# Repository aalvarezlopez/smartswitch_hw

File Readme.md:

# Issues found while testing the first version

* Resisor package is 0201, change it to 0603
* I2C pins are located in a invalid pin. Correct location is:
   * TWD0 SPI\_SDA => PA3 
   * TWCK SPI\_CLK PA4
* I2C pull up resistors are missed (4k7)
* SPI pins are located in a invalid pin. Correct location is:
    * MISO => PA12
    * MOSI => PA13
    * SPCK => PA14
* DS18B20 can be serialized. Hot/Cold temperature of each radiator could use the same bus

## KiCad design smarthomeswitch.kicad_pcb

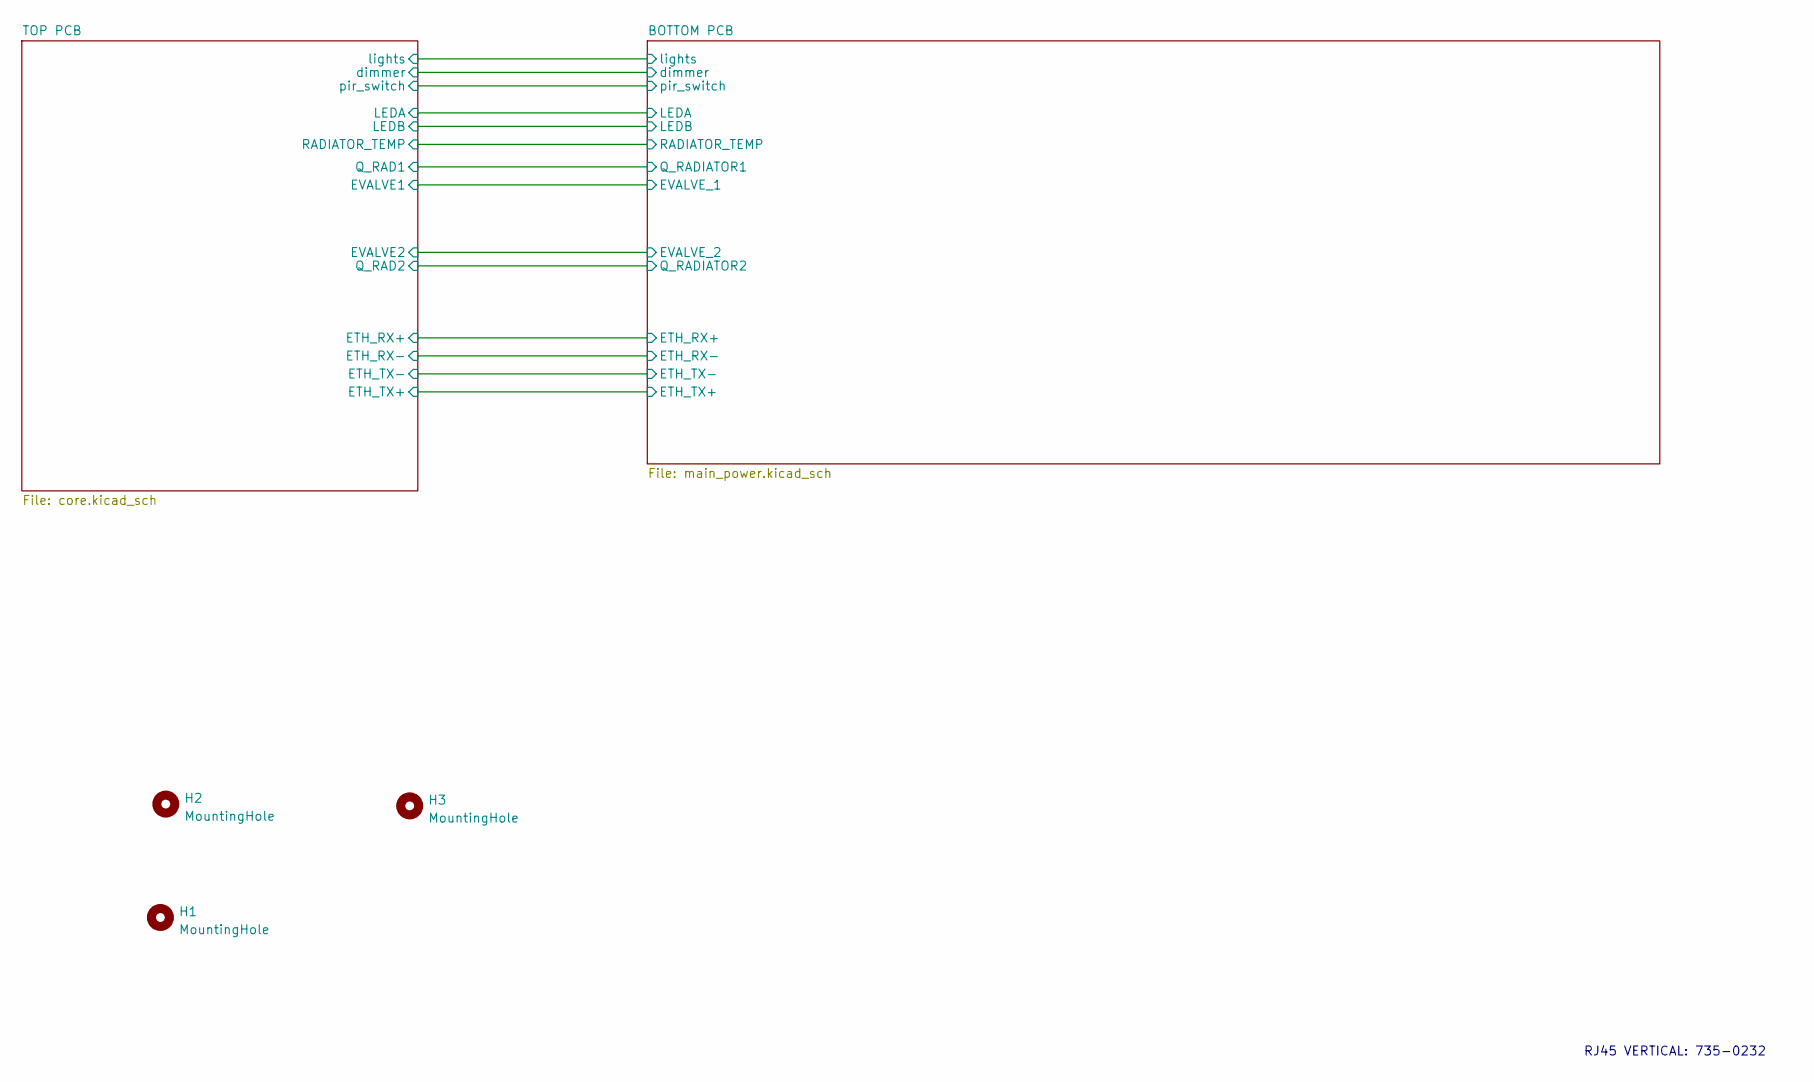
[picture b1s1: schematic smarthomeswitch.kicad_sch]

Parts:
H1, H2, H3: MountingHole; MountingHole_3.2mm_M3_ISO14580

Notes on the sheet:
RJ45 VERTICAL: 735-0232

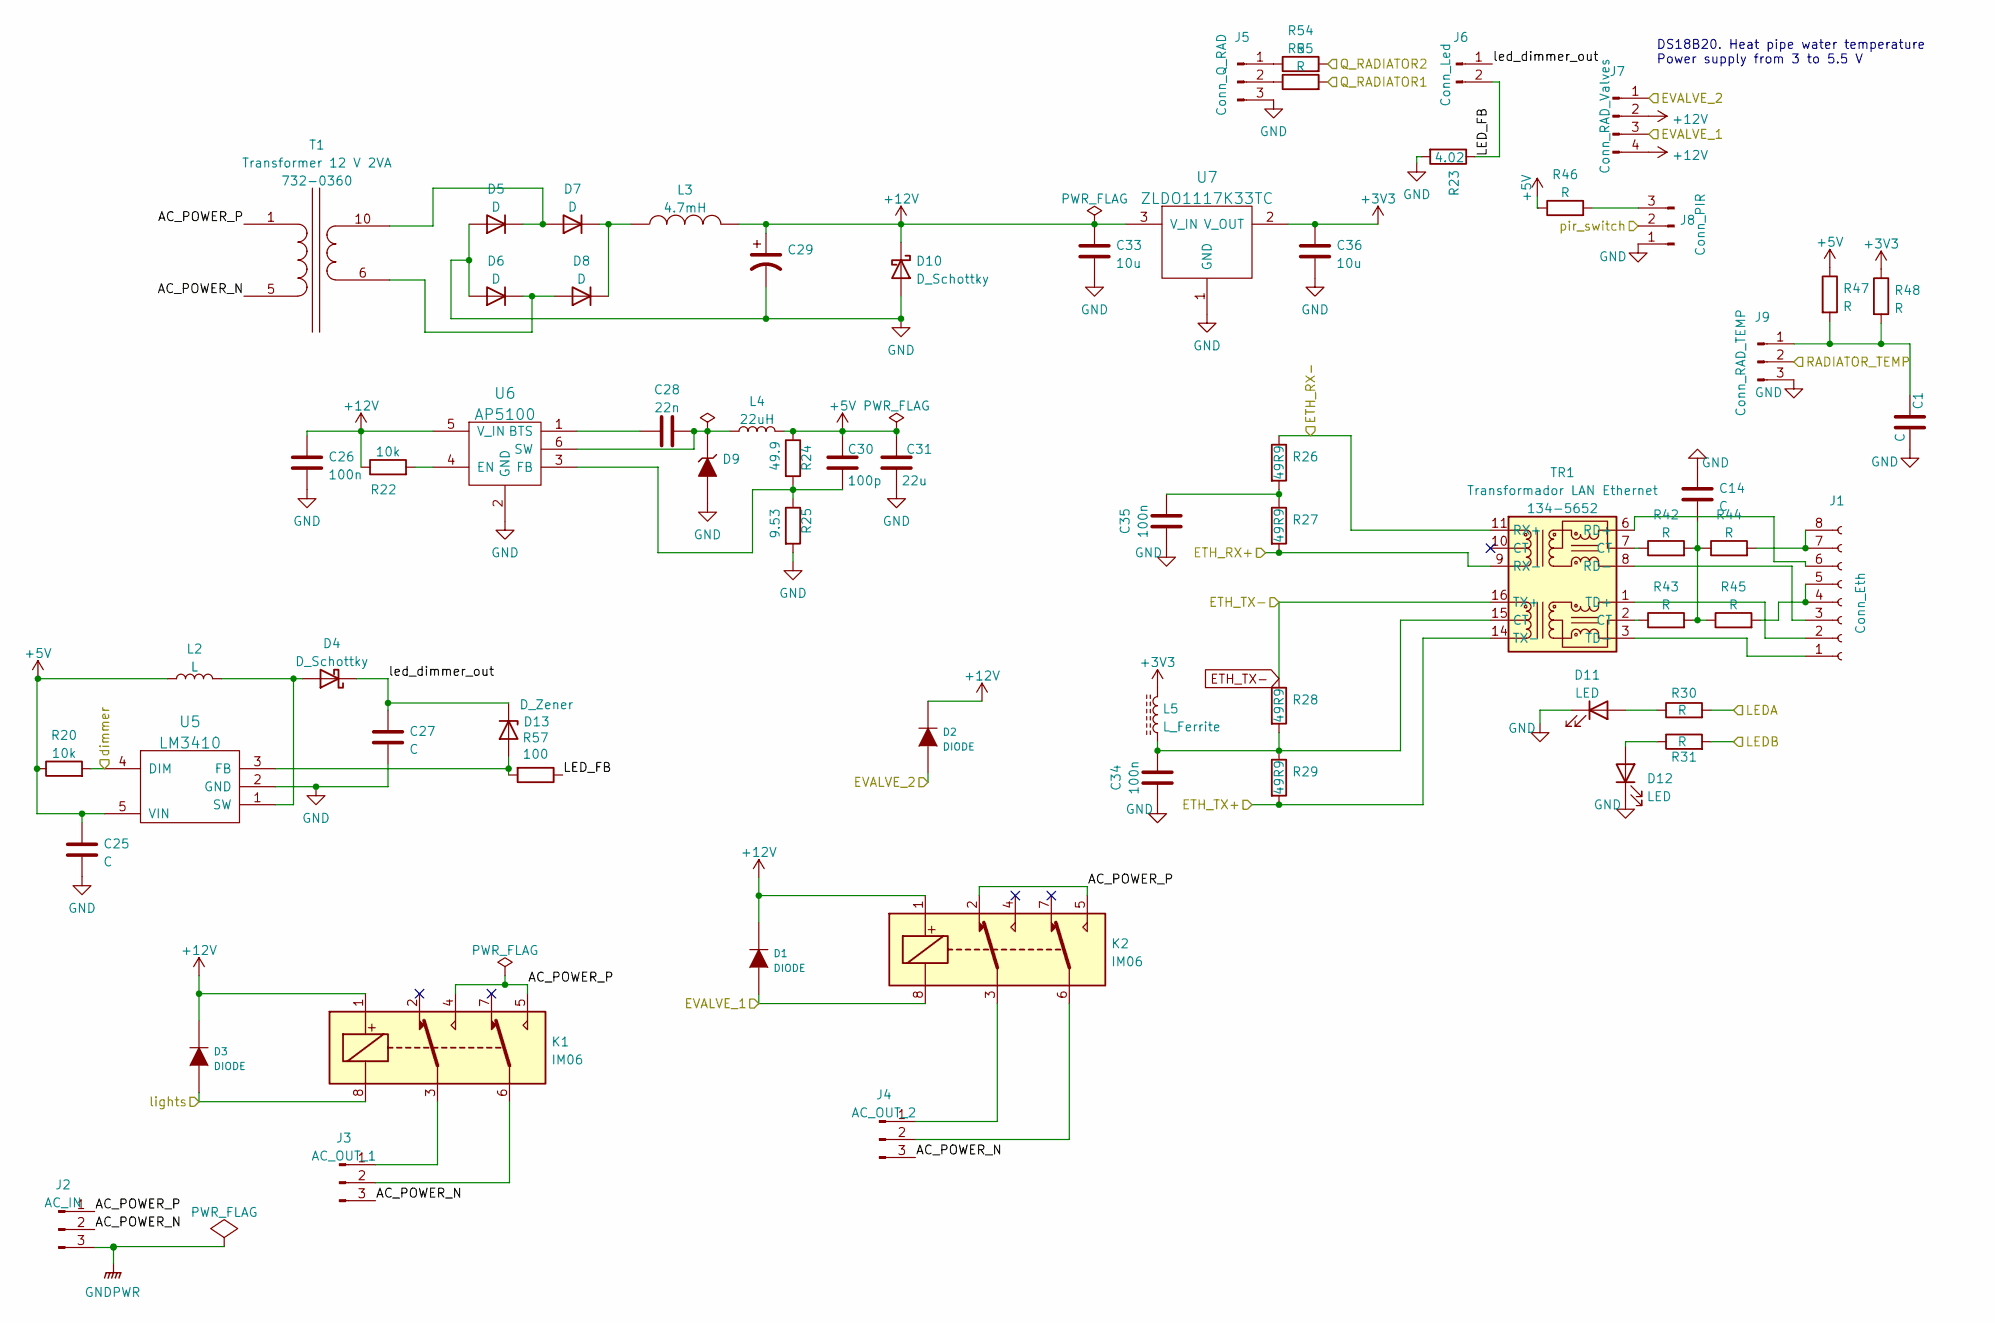
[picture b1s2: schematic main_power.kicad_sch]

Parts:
C1, C14, C25, C27: C; C_0603_1608Metric_Pad1.08x0.95mm_HandSolder
C26, C34, C35: 100n; C_0603_1608Metric_Pad1.08x0.95mm_HandSolder
C28: 22n; C_0603_1608Metric_Pad1.08x0.95mm_HandSolder
C29: C_Polarized_US; CP_Elec_6.3x5.8
C30: 100p; C_0603_1608Metric_Pad1.08x0.95mm_HandSolder
C31: 22u; CP_EIA-6032-15_Kemet-U_Pad2.25x2.35mm_HandSolder
C33, C36: 10u; CP_EIA-3528-12_Kemet-T_Pad1.50x2.35mm_HandSolder
D1, D2, D3: DIODE; D_SMA
D4: D_Schottky; D_Powermite2_AK
D5, D6, D7, D8: D; DO-213AB
D9: ZENER; D_SOD-323
D10: D_Schottky; D_SMA
D11, D12: LED; LED_0603_1608Metric_Pad1.05x0.95mm_HandSolder
D13: D_Zener; D_SMA_Handsoldering
J1: Conn_Eth; PinHeader_1x08_P2.54mm_Vertical
J2: AC_IN; TerminalBlock_bornier-3_P5.08mm
J3: AC_OUT_1; TerminalBlock_bornier-3_P5.08mm
J4: AC_OUT_2; TerminalBlock_bornier-3_P5.08mm
J5: Conn_Q_RAD; JST_PH_B3B-PH-K_1x03_P2.00mm_Vertical
J6: Conn_Led; JST_PH_B2B-PH-K_1x02_P2.00mm_Vertical
J7: Conn_RAD_Valves; JST_PH_B4B-PH-K_1x04_P2.00mm_Vertical
J8: Conn_PIR; JST_PH_B3B-PH-K_1x03_P2.00mm_Vertical
J9: Conn_RAD_TEMP; JST_PH_B3B-PH-K_1x03_P2.00mm_Vertical
K1, K2: IM06; IM06CTS
L2: L; L_1210_3225Metric_Pad1.42x2.65mm_HandSolder
L3: 4.7mH; L_12x12mm_H8mm
L4: 22uH; L_Wuerth_WE-PD2-Typ-L
L5: L_Ferrite; L_0805_2012Metric_Pad1.15x1.40mm_HandSolder
R20, R22: 10k; R_0603_1608Metric_Pad0.98x0.95mm_HandSolder
R23: 4.02; R_0603_1608Metric_Pad0.98x0.95mm_HandSolder
R24: 49.9; R_0603_1608Metric_Pad0.98x0.95mm_HandSolder
R25: 9.53; R_0603_1608Metric_Pad0.98x0.95mm_HandSolder
R26, R27, R28, R29: 49R9; R_0603_1608Metric_Pad0.98x0.95mm_HandSolder
R30, R31, R42, R43, R44, R45, R46, R47, R48, R54, R55: R; R_0603_1608Metric_Pad0.98x0.95mm_HandSolder
R57: 100; R_0603_1608Metric_Pad0.98x0.95mm_HandSolder
T1: Transformer 12 V 2VA; 12v_transformer_single
TR1: Transformador LAN Ethernet; SM13072APEL
U5: LM3410; SOT-23-5_HandSoldering
U6: AP5100; SOT26
U7: ZLDO1117K33TC; TO-252-3_TabPin2

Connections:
+3V3: C36.1, L5.2, R48.1, U7.2 (V_OUT); also elsewhere on the board
+5V: C25.1, C30.1, C31.1, L2.1, L4.2, R20.1, R24.1, R46.1, R47.1, U5.5 (VIN)
+12V: C26.1, C29.1, C33.1, D1.2 (K), D2.2 (K), D3.2 (K), D10.1 (K), J7.2, J7.4, K1.1, K2.1, L3.2, R22.1, U6.5 (V_IN), U7.3 (V_IN)
/BOTTOM PCB/AC_POWER_N: J2.2, J3.3, J4.3, T1.5 (AB)
/BOTTOM PCB/AC_POWER_P: J2.1, K1.4, K1.5, K2.2, K2.5, T1.1 (AA)
/BOTTOM PCB/EVALVE_1: D1.1 (A), J7.3, K2.8; also elsewhere on the board
/BOTTOM PCB/EVALVE_2: D2.1 (A), J7.1; also elsewhere on the board
/BOTTOM PCB/LEDA: R30.2; also elsewhere on the board
/BOTTOM PCB/LEDB: R31.2; also elsewhere on the board
/BOTTOM PCB/LED_FB: J6.2, R23.1, R57.1
/BOTTOM PCB/Q_RADIATOR1: R55.2; also elsewhere on the board
/BOTTOM PCB/Q_RADIATOR2: R54.2; also elsewhere on the board
/BOTTOM PCB/RADIATOR_TEMP: J9.2; also elsewhere on the board
/BOTTOM PCB/dimmer: R20.2, U5.4 (DIM); also elsewhere on the board
/BOTTOM PCB/led_dimmer_out: C27.1, D4.1 (K), D13.1 (K), J6.1
/BOTTOM PCB/lights: D3.1 (A), K1.8; also elsewhere on the board
/BOTTOM PCB/pir_switch: J8.2; also elsewhere on the board
/TOP PCB/ethernet/ETH_RX+: R27.2, TR1.9 (RX-); also elsewhere on the board
/TOP PCB/ethernet/ETH_RX-: R26.1, TR1.11 (RX+); also elsewhere on the board
/TOP PCB/ethernet/ETH_TX+: R29.2, TR1.14 (TX-); also elsewhere on the board
ETH_TX-: R28.1, TR1.16 (TX+); also elsewhere on the board
GND: C1.2, C14.1, C25.2, C26.2, C27.2, C29.2, C31.2, C33.2, C34.1, C35.1, C36.2, D5.2 (A), D6.2 (A), D9.2 (A), D10.2 (A), D11.1 (K), D12.1 (K), J5.3, J8.1, J9.3, R23.2, R25.2, U5.2 (GND), U6.2 (GND), U7.1 (GND); also elsewhere on the board
GNDPWR: J2.3
unnamed: C1.1, J9.1, R47.2, R48.2
unnamed: C14.2, R42.2, R43.2, R44.1, R45.1
unnamed: C28.1, U6.1 (BTS)
unnamed: C28.2, D9.1 (K), L4.1, U6.6 (SW)
unnamed: C30.2, R24.2, R25.1, U6.3 (FB)
unnamed: C34.2, L5.1, R28.2, R29.1, TR1.15 (CT)
unnamed: C35.2, R26.2, R27.1
unnamed: D4.2 (A), L2.2, U5.1 (SW)
unnamed: D5.1 (K), D7.2 (A), T1.10 (SA)
unnamed: D6.1 (K), D8.2 (A), T1.6 (SD)
unnamed: D7.1 (K), D8.1 (K), L3.1
unnamed: D11.2 (A), R30.1
unnamed: D12.2 (A), R31.1
unnamed: D13.2 (A), R57.2, U5.3 (FB)
unnamed: J1.1, TR1.3 (TD-)
unnamed: J1.2, TR1.1 (TD+)
unnamed: J1.3, TR1.8 (RD-)
unnamed: J1.4, J1.5, R45.2
unnamed: J1.6, TR1.6 (RD+)
unnamed: J1.7, J1.8, R44.2
unnamed: J3.1, K1.3
unnamed: J3.2, K1.6
unnamed: J4.1, K2.3
unnamed: J4.2, K2.6
unnamed: J5.1, R54.1
unnamed: J5.2, R55.1
unnamed: J8.3, R46.2
unnamed: R22.2, U6.4 (EN)
unnamed: R42.1, TR1.7 (CT)
unnamed: R43.1, TR1.2 (CT)

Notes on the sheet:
DS18B20. Heat pipe water temperature Power supply from 3 to 5.5 V

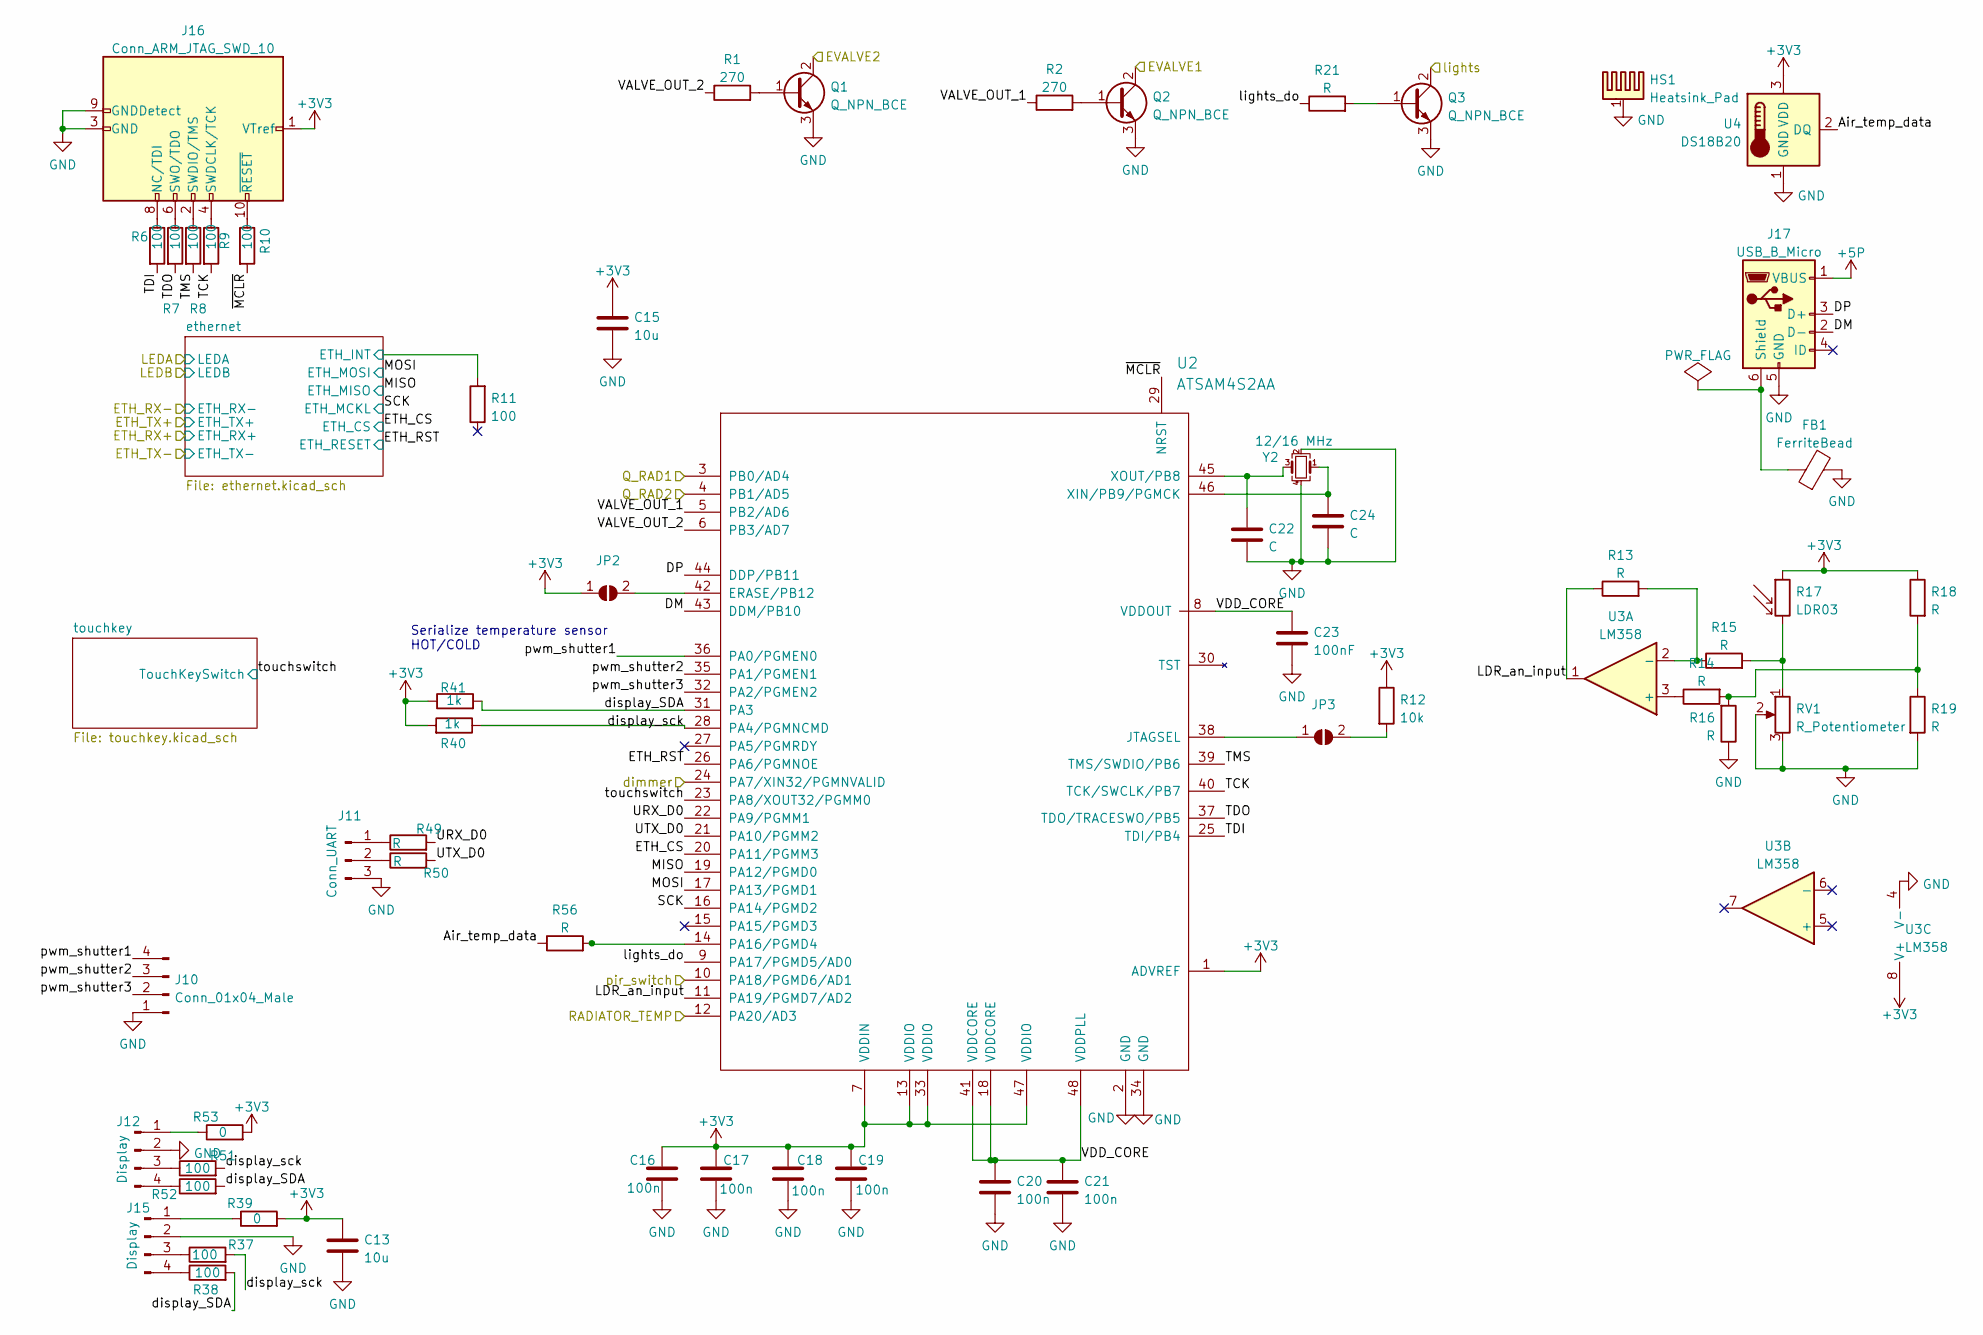
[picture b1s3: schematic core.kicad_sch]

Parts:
C13, C15: 10u; CP_EIA-3528-12_Kemet-T_Pad1.50x2.35mm_HandSolder
C16, C17, C18, C19, C20, C21: 100n; C_0603_1608Metric_Pad1.08x0.95mm_HandSolder
C22, C24: C; C_0603_1608Metric_Pad1.08x0.95mm_HandSolder
C23: 100nF; C_0603_1608Metric_Pad1.08x0.95mm_HandSolder
FB1: FerriteBead; L_1206_3216Metric_Pad1.22x1.90mm_HandSolder
HS1: Heatsink_Pad; Heatsink_AAVID_573300D00010G_TO-263
J10: Conn_01x04_Male; JST_PH_B4B-PH-K_1x04_P2.00mm_Vertical
J11: Conn_UART; JST_PH_B3B-PH-K_1x03_P2.00mm_Vertical
J12, J15: Display; PinHeader_1x04_P2.54mm_Vertical
J16: Conn_ARM_JTAG_SWD_10; JTAG_50mil
J17: USB_B_Micro; USB_Micro-B_Molex_47346-0001
JP2, JP3: SolderJumper_2_Open; SolderJumper-2_P1.3mm_Open_TrianglePad1.0x1.5mm
Q1, Q2, Q3: Q_NPN_BCE; SOT-223-3_TabPin2
R1, R2: 270; R_0603_1608Metric_Pad0.98x0.95mm_HandSolder
R6, R7, R8, R9, R10, R11, R37, R38, R51, R52: 100; R_0603_1608Metric_Pad0.98x0.95mm_HandSolder
R12: 10k; R_0603_1608Metric_Pad0.98x0.95mm_HandSolder
R13, R14, R15, R16, R18, R19, R21, R49, R50, R56: R; R_0603_1608Metric_Pad0.98x0.95mm_HandSolder
R17: LDR03; R_Axial_DIN0204_L3.6mm_D1.6mm_P1.90mm_Vertical
R39, R53: 0; R_0603_1608Metric_Pad0.98x0.95mm_HandSolder
R40, R41: 1k; R_0603_1608Metric_Pad0.98x0.95mm_HandSolder
RV1: R_Potentiometer; Potentiometer_Bourns_TC33X_Vertical
U2: ATSAM4S2AA; LQFP-48_7x7mm_P0.5mm
U3: LM358; SOIC-8_3.9x4.9mm_P1.27mm
U4: DS18B20; TO-92_Inline
Y2: 12/16 MHz; Crystal_SMD_5032-4Pin_5.0x3.2mm

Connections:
+3V3: C13.1, C15.1, C16.1, C17.1, C18.1, C19.1, J16.1 (VTref), JP2.1 (A), R12.1, R17.1, R18.1, R39.2, R40.2, R41.1, R53.2, U2.1 (ADVREF), U2.7 (VDDIN), U2.13 (VDDIO), U2.33 (VDDIO), U2.47 (VDDIO), U3.8 (V+), U4.3 (VDD); also elsewhere on the board
+5P: J17.1 (VBUS)
/BOTTOM PCB/EVALVE_1: Q2.2 (C); also elsewhere on the board
/BOTTOM PCB/EVALVE_2: Q1.2 (C); also elsewhere on the board
/BOTTOM PCB/Q_RADIATOR1: U2.3 (PB0/AD4); also elsewhere on the board
/BOTTOM PCB/Q_RADIATOR2: U2.4 (PB1/AD5); also elsewhere on the board
/BOTTOM PCB/RADIATOR_TEMP: U2.12 (PA20/AD3); also elsewhere on the board
/BOTTOM PCB/dimmer: U2.24 (PA7/XIN32/PGMNVALID); also elsewhere on the board
/BOTTOM PCB/lights: Q3.2 (C); also elsewhere on the board
/BOTTOM PCB/pir_switch: U2.10 (PA18/PGMD6/AD1); also elsewhere on the board
/TOP PCB/Air_temp_data: R56.1, U4.2 (DQ)
/TOP PCB/DM: J17.2 (D-), U2.43 (DDM/PB10)
/TOP PCB/DP: J17.3 (D+), U2.44 (DDP/PB11)
/TOP PCB/ETH_CS: U2.20 (PA11/PGMM3); also elsewhere on the board
/TOP PCB/ETH_RST: U2.26 (PA6/PGMNOE); also elsewhere on the board
/TOP PCB/LDR_an_input: R13.1, U2.11 (PA19/PGMD7/AD2), U3.1
/TOP PCB/MISO: U2.19 (PA12/PGMD0); also elsewhere on the board
/TOP PCB/MOSI: U2.17 (PA13/PGMD1); also elsewhere on the board
/TOP PCB/SCK: U2.16 (PA14/PGMD2); also elsewhere on the board
/TOP PCB/TCK: R9.2, U2.40 (TCK/SWCLK/PB7)
/TOP PCB/TDI: R6.2, U2.25 (TDI/PB4)
/TOP PCB/TDO: R7.2, U2.37 (TDO/TRACESWO/PB5)
/TOP PCB/TMS: R8.2, U2.39 (TMS/SWDIO/PB6)
/TOP PCB/URX_D0: R49.2, U2.22 (PA9/PGMM1)
/TOP PCB/UTX_D0: R50.2, U2.21 (PA10/PGMM2)
/TOP PCB/VALVE_OUT_1: R2.1, U2.5 (PB2/AD6)
/TOP PCB/VALVE_OUT_2: R1.1, U2.6 (PB3/AD7)
/TOP PCB/VDD_CORE: C20.1, C21.1, C23.1, U2.8 (VDDOUT), U2.18 (VDDCORE), U2.41 (VDDCORE), U2.48 (VDDPLL)
/TOP PCB/display_SDA: R38.2, R41.2, R52.2, U2.31 (PA3)
/TOP PCB/display_sck: R37.2, R40.1, R51.2, U2.28 (PA4/PGMNCMD)
/TOP PCB/ethernet/ETH_INT: R11.2; also elsewhere on the board
/TOP PCB/lights_do: R21.1, U2.9 (PA17/PGMD5/AD0)
/TOP PCB/pwm_shutter1: J10.4, U2.36 (PA0/PGMEN0)
/TOP PCB/pwm_shutter2: J10.3, U2.35 (PA1/PGMEN1)
/TOP PCB/pwm_shutter3: J10.2, U2.32 (PA2/PGMEN2)
/TOP PCB/touchswitch: U2.23 (PA8/XOUT32/PGMM0); also elsewhere on the board
/TOP PCB/~MCLR: R10.2, U2.29 (NRST)
GND: C13.2, C15.2, C16.2, C17.2, C18.2, C19.2, C20.2, C21.2, C22.2, C23.2, C24.2, FB1.2, HS1.1, J10.1, J11.3, J12.2, J15.2, J16.3 (GND), J16.5 (GND), J16.9 (GNDDetect), J17.5 (GND), Q1.3 (E), Q2.3 (E), Q3.3 (E), R16.1, R19.2, RV1.2, RV1.3, U2.2 (GND), U2.34 (GND), U3.4 (V-), U4.1 (GND), Y2.2, Y2.4; also elsewhere on the board
unnamed: C22.1, U2.45 (XOUT/PB8), Y2.3
unnamed: C24.1, U2.46 (XIN/PB9/PGMCK), Y2.1
unnamed: FB1.1, J17.6 (Shield)
unnamed: J11.1, R49.1
unnamed: J11.2, R50.1
unnamed: J12.1, R53.1
unnamed: J12.3, R51.1
unnamed: J12.4, R52.1
unnamed: J15.1, R39.1
unnamed: J15.3, R37.1
unnamed: J15.4, R38.1
unnamed: J16.2 (SWDIO/TMS), R8.1
unnamed: J16.4 (SWDCLK/TCK), R9.1
unnamed: J16.6 (SWO/TDO), R7.1
unnamed: J16.8 (NC/TDI), R6.1
unnamed: J16.10 (~RESET), R10.1
unnamed: JP2.2 (B), U2.42 (ERASE/PB12)
unnamed: JP3.1 (A), U2.38 (JTAGSEL)
unnamed: JP3.2 (B), R12.2
unnamed: Q1.1 (B), R1.2
unnamed: Q2.1 (B), R2.2
unnamed: Q3.1 (B), R21.2
unnamed: R13.2, R15.1, U3.2 (-)
unnamed: R14.1, U3.3 (+)
unnamed: R14.2, R16.2, R18.2, R19.1
unnamed: R15.2, R17.2, RV1.1
unnamed: R56.2, U2.14 (PA16/PGMD4)

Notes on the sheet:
Serialize temperature sensor HOT/COLD

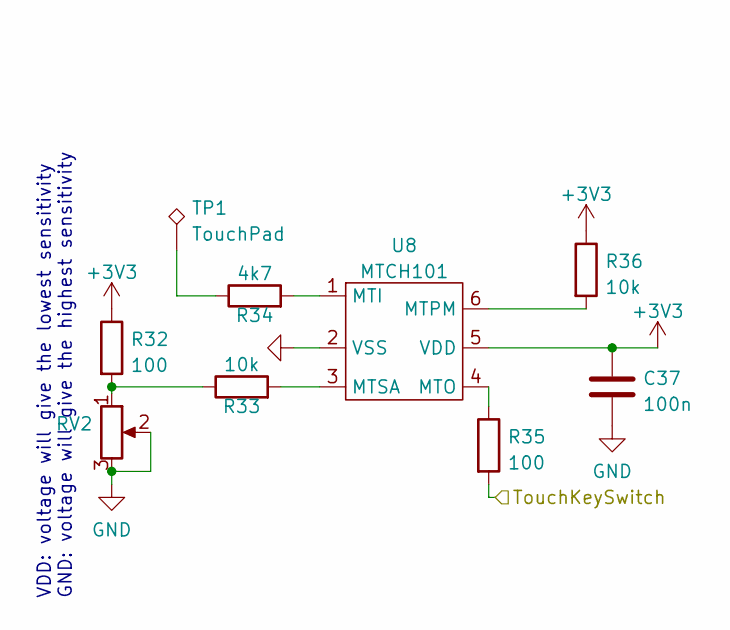
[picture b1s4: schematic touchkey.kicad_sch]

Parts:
C37: 100n; C_0603_1608Metric_Pad1.08x0.95mm_HandSolder
R32, R35: 100; R_0603_1608Metric_Pad0.98x0.95mm_HandSolder
R33, R36: 10k; R_0603_1608Metric_Pad0.98x0.95mm_HandSolder
R34: 4k7; R_0603_1608Metric_Pad0.98x0.95mm_HandSolder
RV2: R_Potentiometer; Potentiometer_Bourns_TC33X_Vertical
TP1: TouchPad; SolderWire-0.15sqmm_1x01_D0.5mm_OD1.5mm
U8: MTCH101; SOT-23-6_Handsoldering

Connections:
+3V3: C37.1, R32.1, R36.1, U8.5 (VDD); also elsewhere on the board
/TOP PCB/touchswitch: R35.2; also elsewhere on the board
GND: C37.2, RV2.2, RV2.3, U8.2 (VSS); also elsewhere on the board
unnamed: R32.2, R33.1, RV2.1
unnamed: R33.2, U8.3 (MTSA)
unnamed: R34.1, TP1.1
unnamed: R34.2, U8.1 (MTI)
unnamed: R35.1, U8.4 (MTO)
unnamed: R36.2, U8.6 (MTPM)

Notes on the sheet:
VDD: voltage will give the lowest sensitivity GND: voltage will give the highest sensitivity

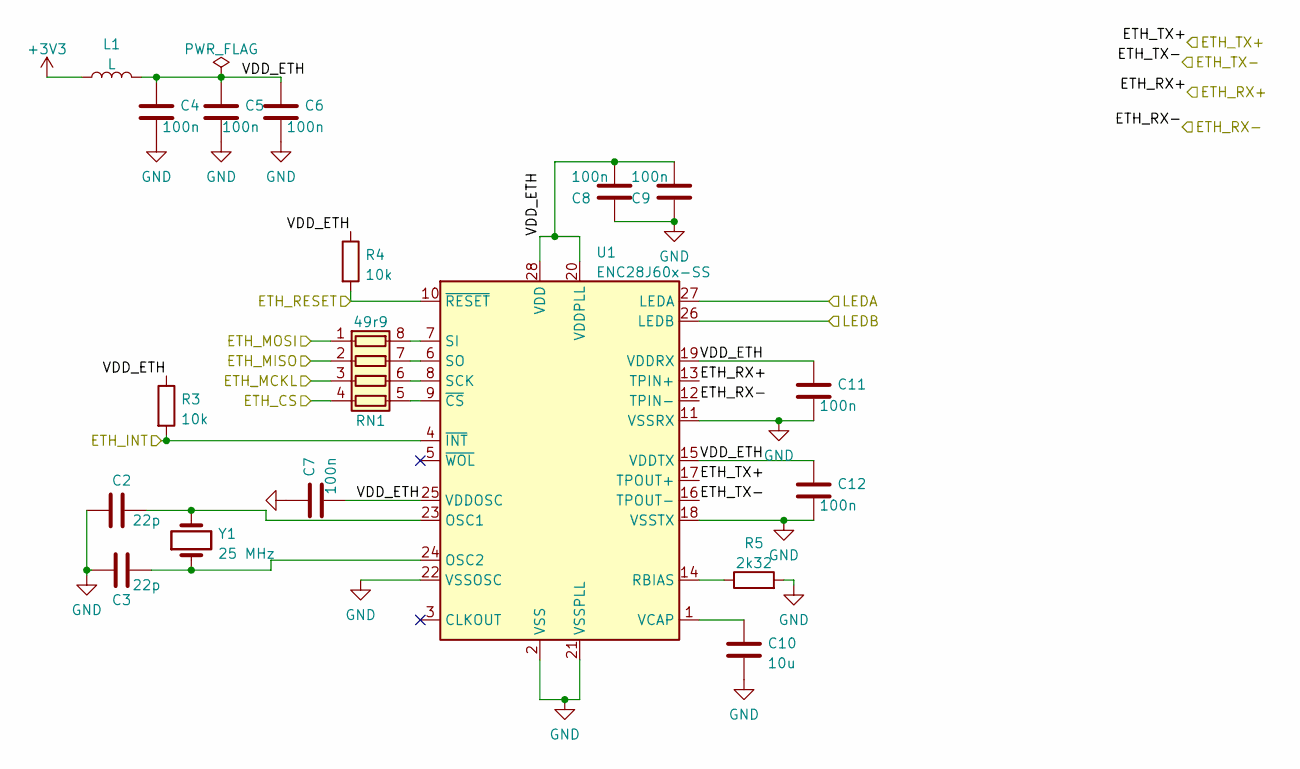
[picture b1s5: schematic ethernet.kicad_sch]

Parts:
C2, C3: 22p; C_0603_1608Metric_Pad1.08x0.95mm_HandSolder
C4, C5, C6, C7, C8, C9, C11, C12: 100n; C_0603_1608Metric_Pad1.08x0.95mm_HandSolder
C10: 10u; CP_EIA-3528-21_Kemet-B_Pad1.50x2.35mm_HandSolder
L1: L; L_0603_1608Metric_Pad1.05x0.95mm_HandSolder
R3, R4: 10k; R_0603_1608Metric_Pad0.98x0.95mm_HandSolder
R5: 2k32; R_0603_1608Metric_Pad0.98x0.95mm_HandSolder
RN1: 49r9; R_Array_Convex_4x0612
U1: ENC28J60x-SS; SSOP-28_5.3x10.2mm_P0.65mm
Y1: 25 MHz; Crystal_SMD_HC49-SD

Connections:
+3V3: L1.1; also elsewhere on the board
/BOTTOM PCB/LEDA: U1.27 (LEDA); also elsewhere on the board
/BOTTOM PCB/LEDB: U1.26 (LEDB); also elsewhere on the board
/TOP PCB/ETH_CS: RN1.4 (R4.1); also elsewhere on the board
/TOP PCB/ETH_RST: R4.2, U1.10 (~RESET); also elsewhere on the board
/TOP PCB/MISO: RN1.2 (R2.1); also elsewhere on the board
/TOP PCB/MOSI: RN1.1 (R1.1); also elsewhere on the board
/TOP PCB/SCK: RN1.3 (R3.1); also elsewhere on the board
/TOP PCB/ethernet/ETH_INT: R3.2, U1.4 (~INT); also elsewhere on the board
/TOP PCB/ethernet/ETH_RX+: U1.13 (TPIN+); also elsewhere on the board
/TOP PCB/ethernet/ETH_RX-: U1.12 (TPIN-); also elsewhere on the board
/TOP PCB/ethernet/ETH_TX+: U1.17 (TPOUT+); also elsewhere on the board
/TOP PCB/ethernet/VDD_ETH: C4.1, C5.1, C6.1, C7.2, C8.2, C9.2, C11.1, C12.1, L1.2, R3.1, R4.1, U1.15 (VDDTX), U1.19 (VDDRX), U1.20 (VDDPLL), U1.25 (VDDOSC), U1.28 (VDD)
ETH_TX-: U1.16 (TPOUT-); also elsewhere on the board
GND: C2.1, C3.1, C4.2, C5.2, C6.2, C7.1, C8.1, C9.1, C10.2, C11.2, C12.2, R5.2, U1.2 (VSS), U1.11 (VSSRX), U1.18 (VSSTX), U1.21 (VSSPLL), U1.22 (VSSOSC); also elsewhere on the board
unnamed: C2.2, U1.23 (OSC1), Y1.2
unnamed: C3.2, U1.24 (OSC2), Y1.1
unnamed: C10.1, U1.1 (VCAP)
unnamed: R5.1, U1.14 (RBIAS)
unnamed: RN1.5 (R4.2), U1.9 (~CS)
unnamed: RN1.6 (R3.2), U1.8 (SCK)
unnamed: RN1.7 (R2.2), U1.6 (SO)
unnamed: RN1.8 (R1.2), U1.7 (SI)

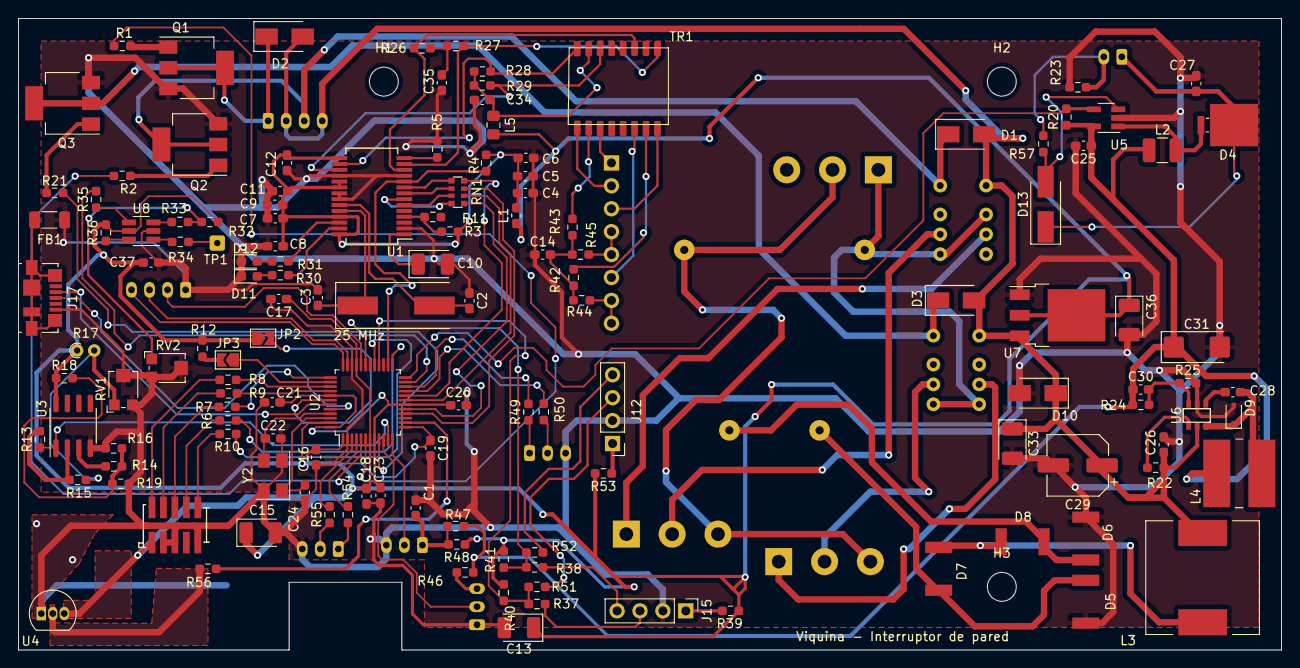
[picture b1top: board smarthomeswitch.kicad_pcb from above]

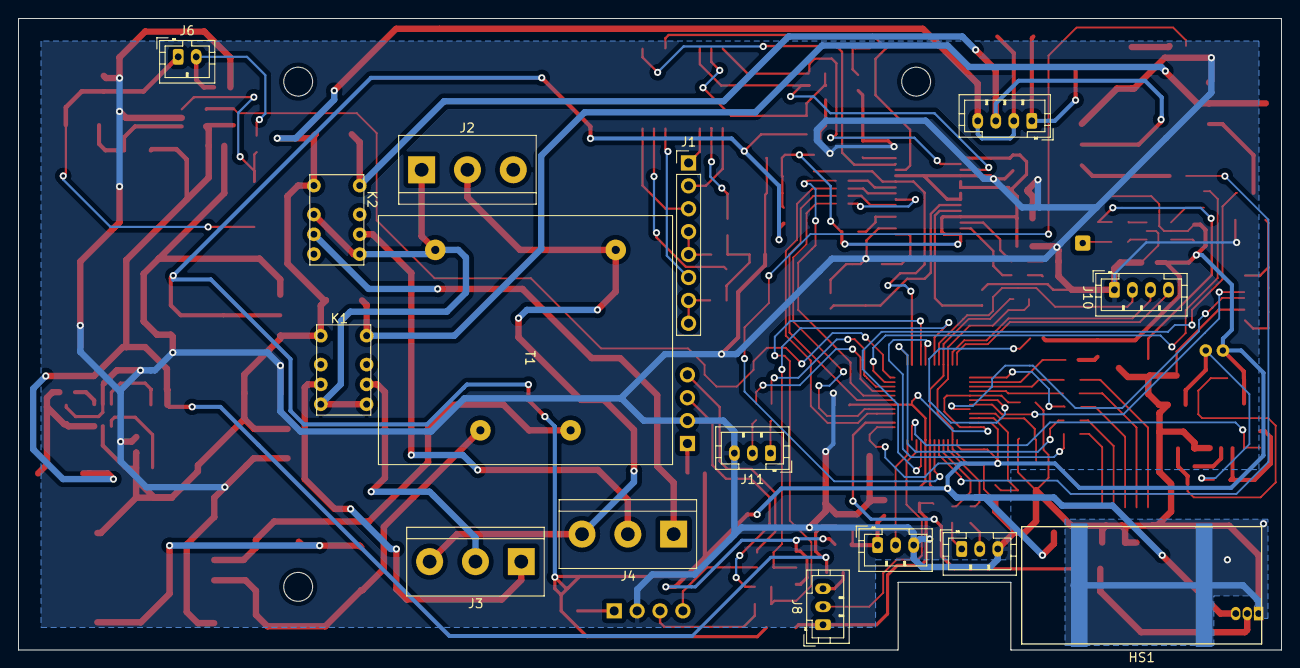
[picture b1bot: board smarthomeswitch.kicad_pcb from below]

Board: 2 copper layers, 140.0 x 70.0 mm, 154 parts (15 on the bottom side), 121 nets.

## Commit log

2023-11-25 First commit. First version with lot of issues
2023-11-25 Adding gitignore and cleaning project
2024-11-10 Second version
2024-11-10 Adding subcomponents
